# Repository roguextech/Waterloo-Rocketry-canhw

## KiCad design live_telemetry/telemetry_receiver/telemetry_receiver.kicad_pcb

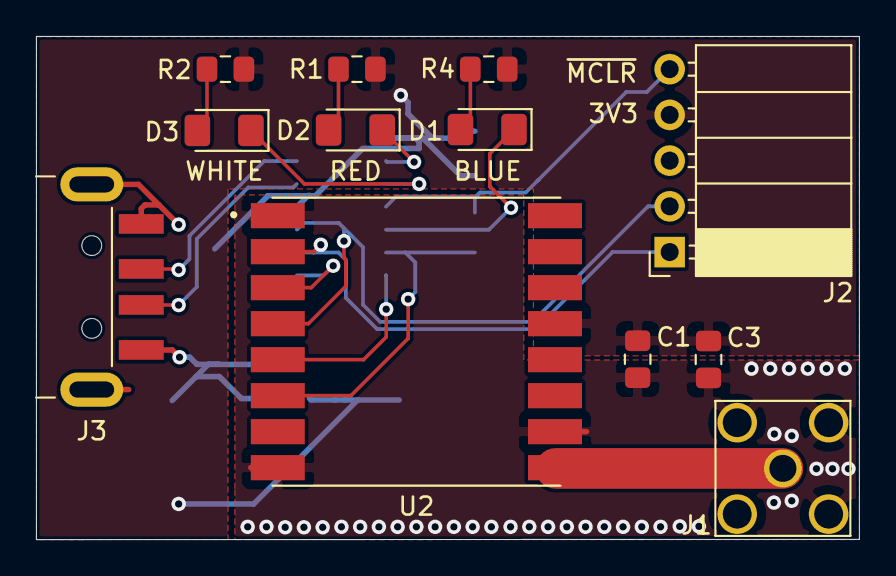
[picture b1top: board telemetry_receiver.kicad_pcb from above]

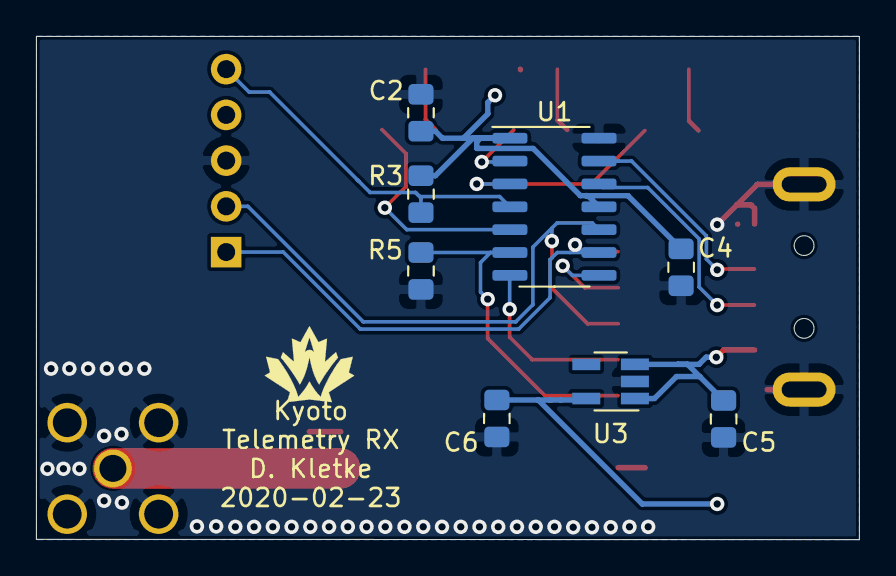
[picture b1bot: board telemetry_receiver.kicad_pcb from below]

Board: 2 copper layers, 45.7 x 28.0 mm, 20 parts (8 on the bottom side), 18 nets.

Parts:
C1: 100p; C_0805_2012Metric_Pad1.15x1.40mm_HandSolder
C2, C3: 0.1u; C_0805_2012Metric_Pad1.15x1.40mm_HandSolder
C4: 0.47u; C_0805_2012Metric_Pad1.15x1.40mm_HandSolder
C5, C6: 4.7u; C_0805_2012Metric_Pad1.15x1.40mm_HandSolder
D1, D2, D3: LED; LED_1206_3216Metric_Pad1.42x1.75mm_HandSolder
J1: Conn_Coaxial; RF_connector_SMA_3-1478978-1
J2: Programming Header; PinSocket_1x05_P2.54mm_Horizontal
J3: USB_A; USB_A_CNCTech_1001-011-01101_Horizontal
R1, R2, R4: 130; R_0805_2012Metric_Pad1.15x1.40mm_HandSolder
R3, R5: 10k; R_0805_2012Metric_Pad1.15x1.40mm_HandSolder
U1: PIC16LF1455; SOIC-14_3.9x8.7mm_P1.27mm
U2: RFM95W; XCVR_RFM95W-915S2
U3: AP2114H-3.3; SOT-23-5_HandSoldering

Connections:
+3V3: C1.1, C2.1, C3.1, C4.1, C6.1, J2.4, R1.1, R2.1, R3.1, R4.1, U1.1, U1.11, U2.13, U3.5
+5V: C5.1, J3.1, U3.1, U3.3
/ICSPCLK: J2.1, U1.9, U2.2
/ICSPDAT: J2.2, U1.10, U2.4
/MOSI: U1.8, U2.3
/RESET: R5.1, U1.6, U2.6
/USB_D+: J3.3, U1.13
/USB_D-: J3.2, U1.12
/~MCLR: J2.5, R3.2, U1.4
/~SS: U1.7, U2.5
GND: C1.2, C2.2, C3.2, C4.2, C5.2, C6.2, J1.2, J2.3, J3.4, J3.5, R5.2, U1.14, U2.1, U2.8, U2.10, U3.2
unnamed: J1.1, U2.9
unnamed: D1.1, U1.5
unnamed: D1.2, R4.2
unnamed: D2.1, U1.2
unnamed: D2.2, R1.2
unnamed: D3.1, U1.3
unnamed: D3.2, R2.2

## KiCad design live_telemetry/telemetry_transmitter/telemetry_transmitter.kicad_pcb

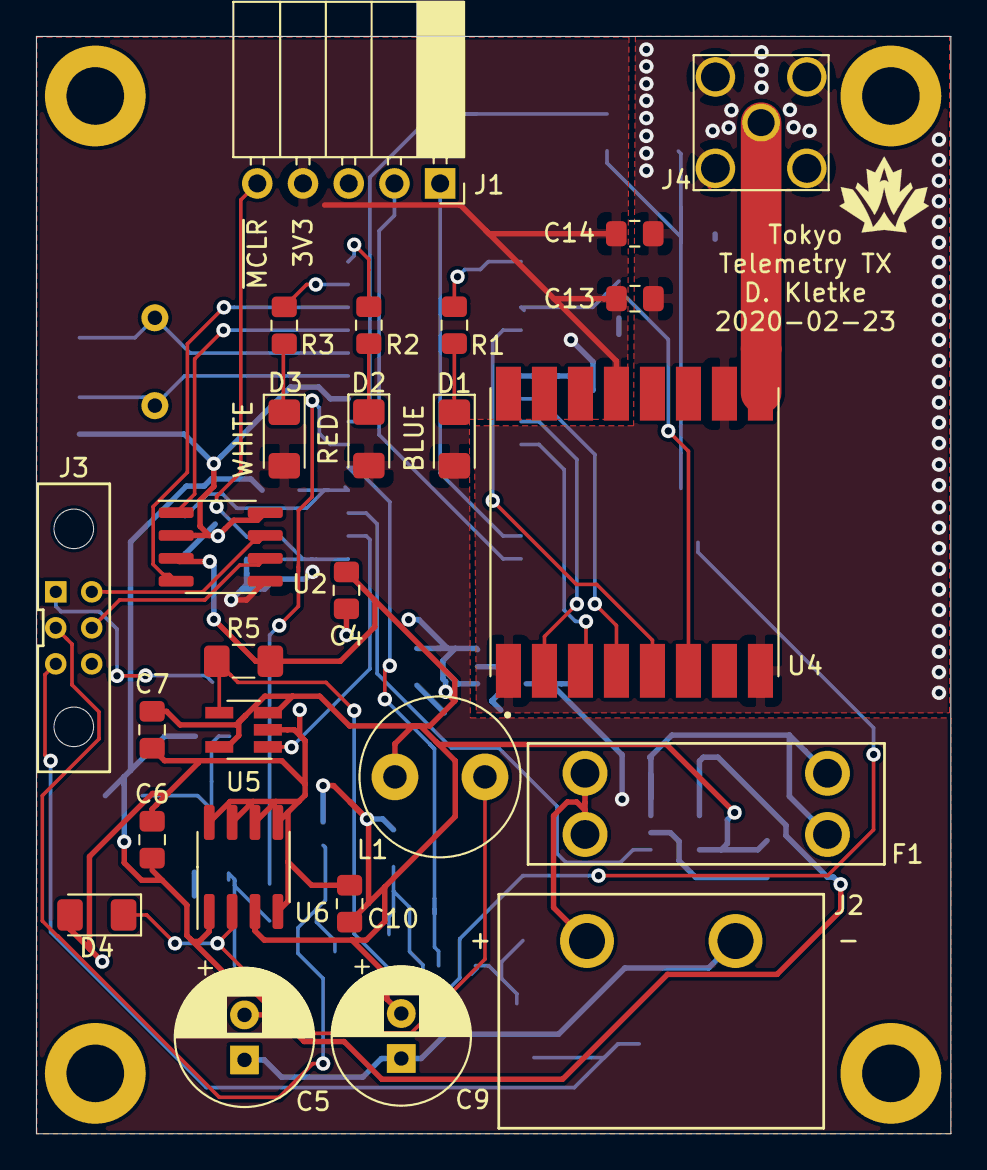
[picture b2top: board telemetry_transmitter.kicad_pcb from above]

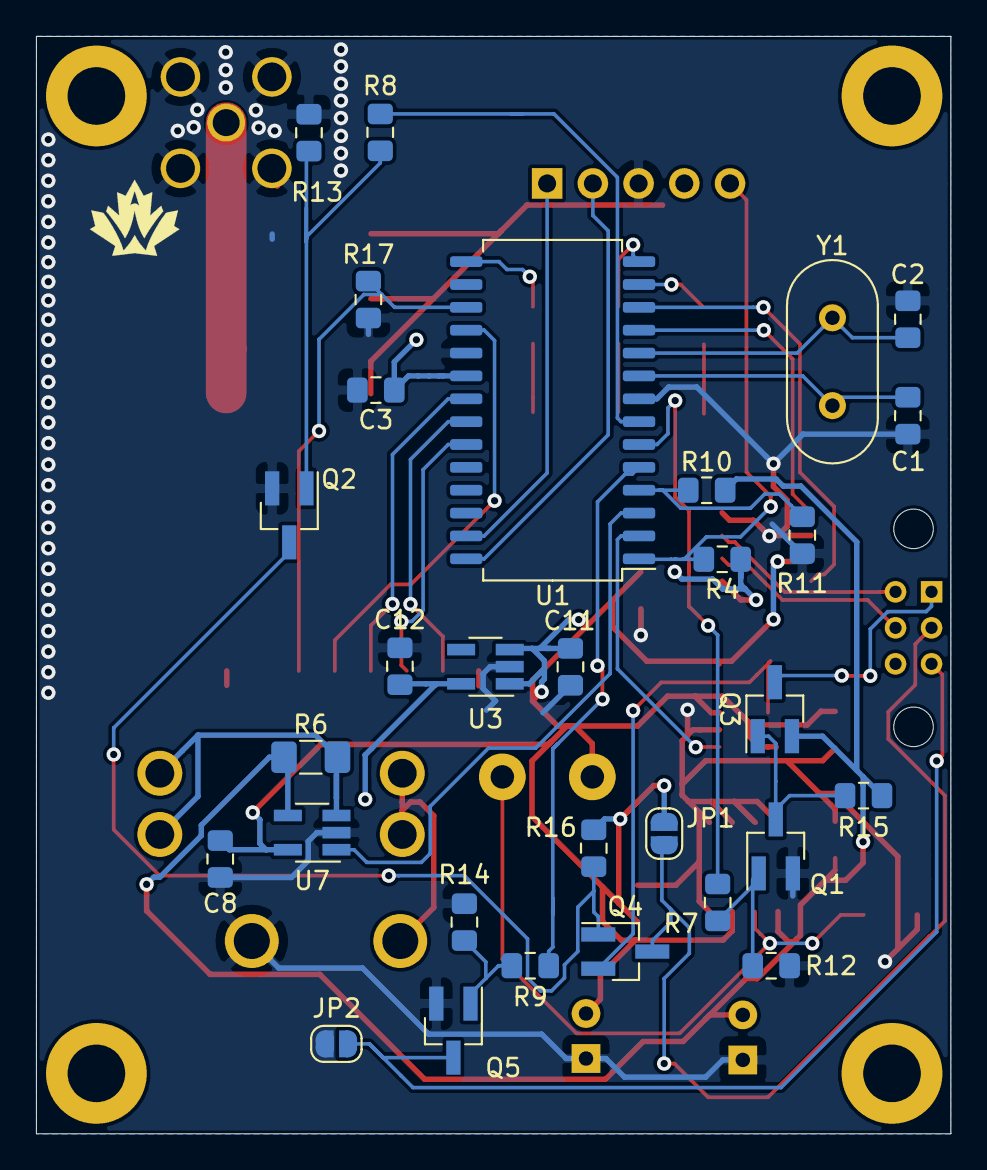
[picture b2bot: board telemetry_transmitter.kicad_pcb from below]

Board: 2 copper layers, 50.8 x 61.0 mm, 56 parts (30 on the bottom side), 43 nets.

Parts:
C1, C2: 26p; C_0805_2012Metric_Pad1.15x1.40mm_HandSolder
C3, C6, C7, C8, C10, C14: 0.1u; C_0805_2012Metric_Pad1.15x1.40mm_HandSolder
C4: 10u; C_0805_2012Metric_Pad1.15x1.40mm_HandSolder
C5: 330u; CP_Radial_D7.5mm_P2.50mm
C9: 1000u; CP_Radial_D7.5mm_P2.50mm
C11, C12: 4.7u; C_0805_2012Metric_Pad1.15x1.40mm_HandSolder
C13: 100p; C_0805_2012Metric_Pad1.15x1.40mm_HandSolder
D1, D2, D3: LED; LED_1206_3216Metric_Pad1.42x1.75mm_HandSolder
D4: D_Zener; D_1206_3216Metric_Pad1.42x1.75mm_HandSolder
F1: Fuse; Fuseholder_36-3557-15-ND
J1: Programming Header; PinSocket_1x05_P2.54mm_Horizontal
J2: Battery In; BarrierBlock_ED2945-ND
J3: BUS_CONN; connector_Harwin_M80-5000642
J4: Conn_Coaxial; RF_connector_SMA_3-1478978-1
JP1, JP2: Jumper; SolderJumper-2_P1.3mm_Open_RoundedPad1.0x1.5mm
L1: 47u; L_Radial_D8.7mm_P5.00mm_Fastron_07HCP
Q1, Q2, Q5: Q_NMOS_GSD; SOT-23_Handsoldering
Q3, Q4: Q_PMOS_GSD; SOT-23_Handsoldering
R1, R2, R3: 130; R_0805_2012Metric_Pad1.15x1.40mm_HandSolder
R4, R12, R13, R14, R15, R16: 10K; R_0805_2012Metric_Pad1.15x1.40mm_HandSolder
R5, R6: R_sense; R_1206_3216Metric_Pad1.42x1.75mm_HandSolder
R7, R8, R9: 220; R_0805_2012Metric_Pad1.15x1.40mm_HandSolder
R10, R11: R; R_0805_2012Metric_Pad1.15x1.40mm_HandSolder
R17: 10k; R_0805_2012Metric_Pad1.15x1.40mm_HandSolder
U1: PIC18F26K83; SOIC-28W_7.5x18.7mm_P1.27mm
U2: MCP2562; SOIC-8_3.9x4.9mm_P1.27mm
U3: AP2114H-3.3; SOT-23-5_HandSoldering
U4: RFM95W; XCVR_RFM95W-915S2
U5, U7: INA180; SOT-23-5_HandSoldering
U6: AP1509; SOIC-8_3.9x4.9mm_P1.27mm
Y1: Crystal; Crystal_HC49-U_Vertical

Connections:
+3V3: C3.1, C12.2, C13.1, C14.1, D1.2, D2.2, D3.2, J1.4, R4.2, U1.20, U2.5, U3.5, U4.13
+5V: C4.1, C7.2, C8.2, C9.2, C10.2, C11.2, JP1.1, L1.2, R5.2, R16.1, U2.3, U3.1, U3.3, U5.3, U5.5, U6.3, U7.5
+12V: C5.2, C6.2, Q3.2, R6.1, R10.1, R15.1, U6.1, U7.4
/CAN_RX: U1.12, U2.4
/CAN_TX: U1.11, U2.1
/ICSPCLK: J1.1, U1.27
/ICSPDAT: J1.2, U1.28
/OSC1: C1.1, U1.9, Y1.1
/OSC2: C2.1, U1.10, Y1.2
/power/BATT_VSENSE: R10.2, R11.1, U1.4
/power/BUS_EN_5V: R8.2, U1.7
/power/BUS_EN_12V: R7.2, U1.6
/power/BUS_EN_GND: R9.2, U1.5
/power/CURR_BATT: U1.3, U7.1
/power/CURR_BUS: U1.2, U5.1
/power/Sensed_5V: Q4.2, R5.1, U5.4
/radio/RESET: R17.1, U1.17, U4.6
/radio/SCK: U1.21, U4.4
/radio/SDI: U1.22, U4.2
/radio/SDO: U1.23, U4.3
/radio/~SS: U1.18, U4.5
/~MCLR: J1.5, R4.1, U1.1
CANH: J3.4, U2.7
CANL: J3.5, U2.6
GND: C1.2, C2.2, C3.2, C4.2, C5.1, C6.1, C7.1, C8.1, C9.1, C10.1, C11.1, C12.1, C13.2, C14.2, D4.2, J1.3, J2.1, J4.2, JP2.2, Q1.2, Q2.2, Q5.2, R11.2, R12.2, R13.2, R14.2, R17.2, U1.8, U1.19, U2.2, U2.8, U3.2, U4.1, U4.8, U4.10, U5.2, U6.4, U6.5, U6.6, U6.7, U6.8, U7.2
unnamed: J4.1, U4.9
unnamed: D1.1, R1.1
unnamed: D2.1, R2.1
unnamed: D3.1, R3.1
unnamed: D4.1, L1.1, U6.2
unnamed: F1.1, R6.2, U7.3
unnamed: F1.2, J2.2
unnamed: J3.1, Q3.3
unnamed: J3.2, JP1.2, Q4.3
unnamed: J3.3, JP2.1, Q5.3
unnamed: Q1.1, R7.1, R12.1
unnamed: Q1.3, Q3.1, R15.2
unnamed: Q2.1, R8.1, R13.1
unnamed: Q2.3, Q4.1, R16.2
unnamed: Q5.1, R9.1, R14.1
unnamed: R1.2, U1.15
unnamed: R2.2, U1.14
unnamed: R3.2, U1.13

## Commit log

2020-03-31 Update schematics and silkscreens to fix issues from assembly
2020-10-06 Fixed vent footprint path
